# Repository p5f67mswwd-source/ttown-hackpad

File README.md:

TTOWN is a 7 key macropad with a rotary encoder, and led backlights. It uses KMK firmware to bind keys to your keyboard. The macropad has a grey top with a darker shade for the base to keep a sleek/minimalstic when combined with the led. Which is all held together by 4 heatset inserts and 4 m3x16mm screws.
LAYOUT:
[][]
[][][][]

Keybinds:
Some keybinds include copy, paste, cut, raise and lower volume, and undo/redo.

Firmware: 
I used KMK firmware through circuit python to code my pcb,you can change/control your keybinds and led colors.

CAD:

PCB

BOM:

An EC11 Rotary encoder for scrolling or volume control
1 unsoldered Seeed XIAO RP2040
7x through-hole 1N4148 Diodes
7x MX-Style switches
1x EC11 Rotary encoders
7x white blank DSA keycaps
7x SK6812 MINI-E LEDs
4x M3x16mm screws
4x M3x5mx4mm heatset inserts

Conclusion:
This project was really tedious and challanging as this was my first ever robotics projects. It helped me learn and design pcbs and how to install firmware. I've also found out what I struggled with and what I need to improve on.

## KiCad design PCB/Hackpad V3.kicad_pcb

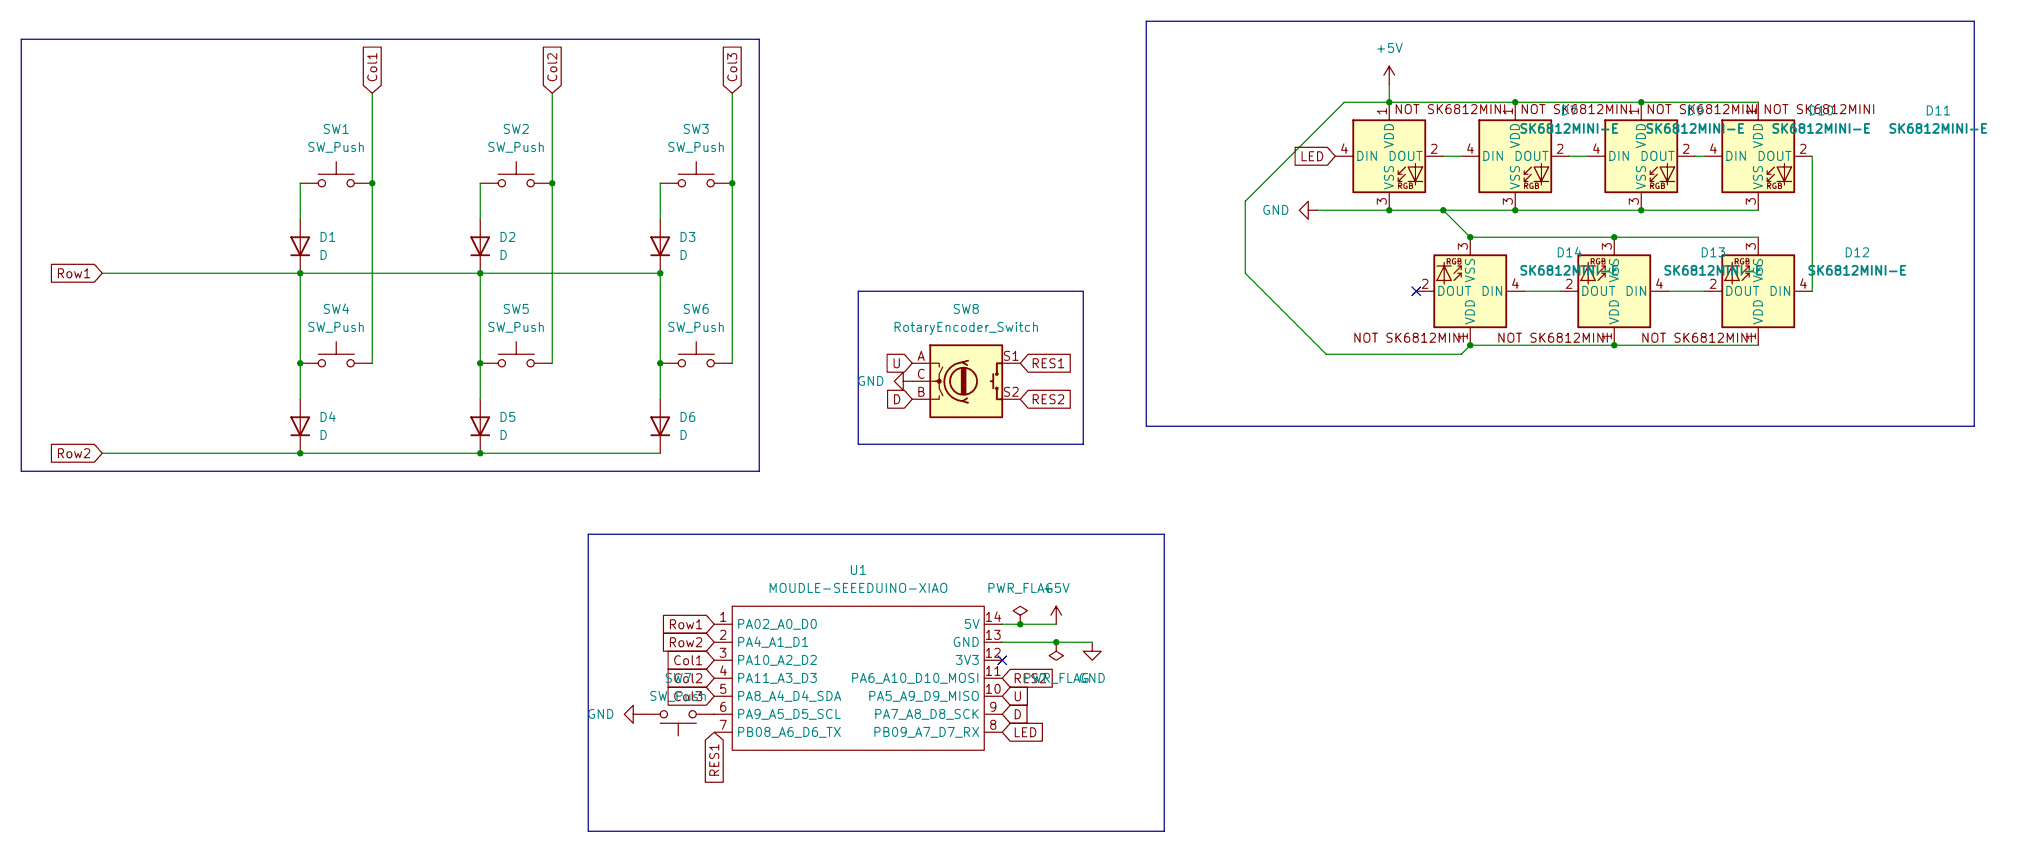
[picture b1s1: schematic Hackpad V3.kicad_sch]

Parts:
D1, D2, D3, D4, D5, D6: D; D_DO-35_SOD27_P7.62mm_Horizontal
D7, D9, D10, D11, D12, D13, D14: SK6812MINI-E; SK6812MINI-E_fixed
SW1, SW2, SW3, SW4, SW5, SW6, SW7: SW_Push; SW_Cherry_MX_1.00u_PCB
SW8: RotaryEncoder_Switch; RotaryEncoder_Alps_EC11E-Switch_Vertical_H20mm
U1: MOUDLE-SEEEDUINO-XIAO; XIAO-Generic-Hybrid-14P-2.54-21X17.8MM

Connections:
+5V: D7.1 (VDD), D9.1 (VDD), D10.1 (VDD), D11.1 (VDD), D12.1 (VDD), D13.1 (VDD), D14.1 (VDD), U1.14 (5V)
Col1: SW1.2, SW4.2, U1.3 (PA10_A2_D2)
Col2: SW2.2, SW5.2, U1.4 (PA11_A3_D3)
Col3: SW3.2, SW6.2, U1.5 (PA8_A4_D4_SDA)
D: SW8.B, U1.9 (PA7_A8_D8_SCK)
GND: D7.3 (VSS), D9.3 (VSS), D10.3 (VSS), D11.3 (VSS), D12.3 (VSS), D13.3 (VSS), D14.3 (VSS), SW7.2, SW8.C, U1.13 (GND)
LED: D7.4 (DIN), U1.8 (PB09_A7_D7_RX)
unnamed: D1.2 (A), SW1.1
unnamed: D2.2 (A), SW2.1
unnamed: D3.2 (A), SW3.1
unnamed: D7.2 (DOUT), D9.4 (DIN)
unnamed: D9.2 (DOUT), D10.4 (DIN)
unnamed: D10.2 (DOUT), D11.4 (DIN)
unnamed: D11.2 (DOUT), D12.4 (DIN)
unnamed: D12.2 (DOUT), D13.4 (DIN)
unnamed: D13.2 (DOUT), D14.4 (DIN)
unnamed: SW7.1, U1.6 (PA9_A5_D5_SCL)
RES1: SW8.S1, U1.7 (PB08_A6_D6_TX)
RES2: SW8.S2, U1.11 (PA6_A10_D10_MOSI)
Row1: D1.1 (K), D2.1 (K), D3.1 (K), D4.2 (A), D5.2 (A), D6.2 (A), SW4.1, SW5.1, SW6.1, U1.1 (PA02_A0_D0)
Row2: D4.1 (K), D5.1 (K), D6.1 (K), U1.2 (PA4_A1_D1)
U: SW8.A, U1.10 (PA5_A9_D9_MISO)

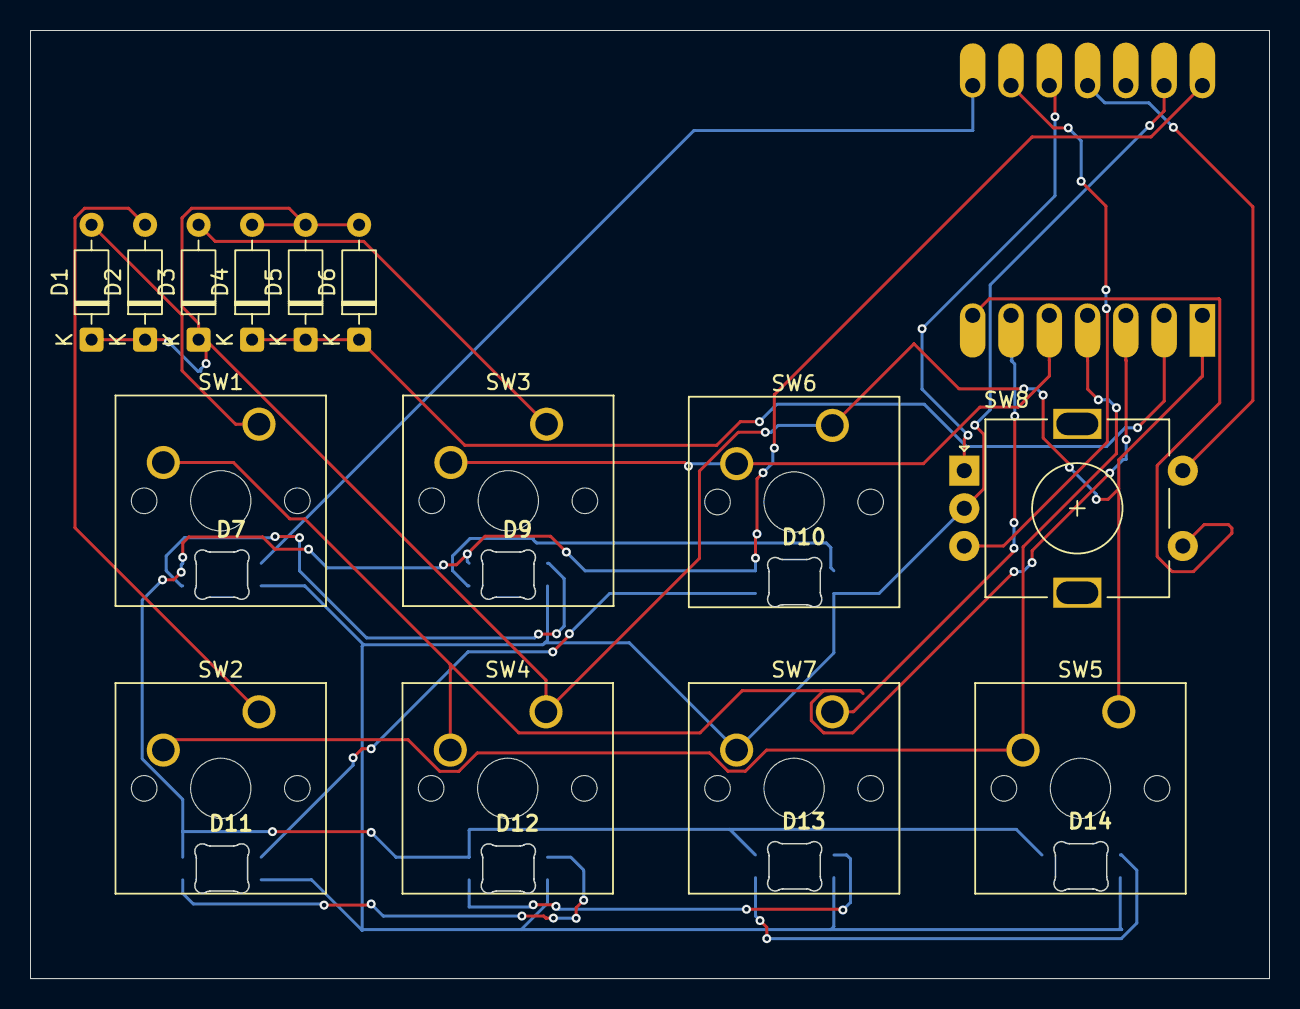
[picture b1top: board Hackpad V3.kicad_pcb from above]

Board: 2 copper layers, 82.2 x 62.9 mm, 22 parts (1 on the bottom side), 22 nets.
